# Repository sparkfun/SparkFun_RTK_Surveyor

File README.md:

SparkFun RTK Surveyor - Hardware
===========================================================

[*SparkFun RTK Surveyor (SPX-17369)*](https://www.sparkfun.com/products/17369)

The SparkFun RTK Surveyor is an easy to use GNSS receiver for centimeter-level positioning. Perfect for surveying, this preprogrammed device can also be used for autonomous driving, navigation, asset tracking and any other application where there is a clear view of the sky. The RTK Surveyor can also be used as a base station. With the flick of a switch, two RTK Surveyors can be used to create an RTK system capable of 14mm horizontal positional accuracy. The built-in Bluetooth connection via an ESP32 WROOM enables the user to use the RTK Surveyor with their choice of GIS application on a phone or tablet. The built in battery allows field use for up to four hours and is compatible with common USB battery banks.

This repo houses the hardware for the product including the PCB design, enclosure, and graphic overlay. The firmware for the RTK Surveyor (and other SparkFun RTK products) can be found [here](https://github.com/sparkfun/SparkFun_RTK_Firmware).

SparkFun labored with love to create this product. Feel like supporting open source hardware? 
[Buy a product](https://www.sparkfun.com/products/17369) from SparkFun!

Repository Contents
-------------------

* **/Documents** - Documentation on hardware and 3D files for the enclosure
* **/Enclosure** - gcode for enclosure milling
* **/Graphics** - Bitmaps for display (not currently implmented)
* **/Hardware** - Eagle files

Documentation
--------------

* **[Hookup Guide](https://learn.sparkfun.com/tutorials/sparkfun-rtk-surveyor-hookup-guide)** - Hookup guide for the SparkFun RTK Surveyor.

License Information
-------------------

This product is _**open source**_!

Various bits of the code have different licenses applied. Anything SparkFun wrote is beerware; if you see me (or any other SparkFun employee) at the local, and you've found our code helpful, please buy us a round!

Please use, reuse, and modify these files as you see fit. Please maintain attribution to SparkFun Electronics and release anything derivative under the same license.

Distributed as-is; no warranty is given.

- Your friends at SparkFun.

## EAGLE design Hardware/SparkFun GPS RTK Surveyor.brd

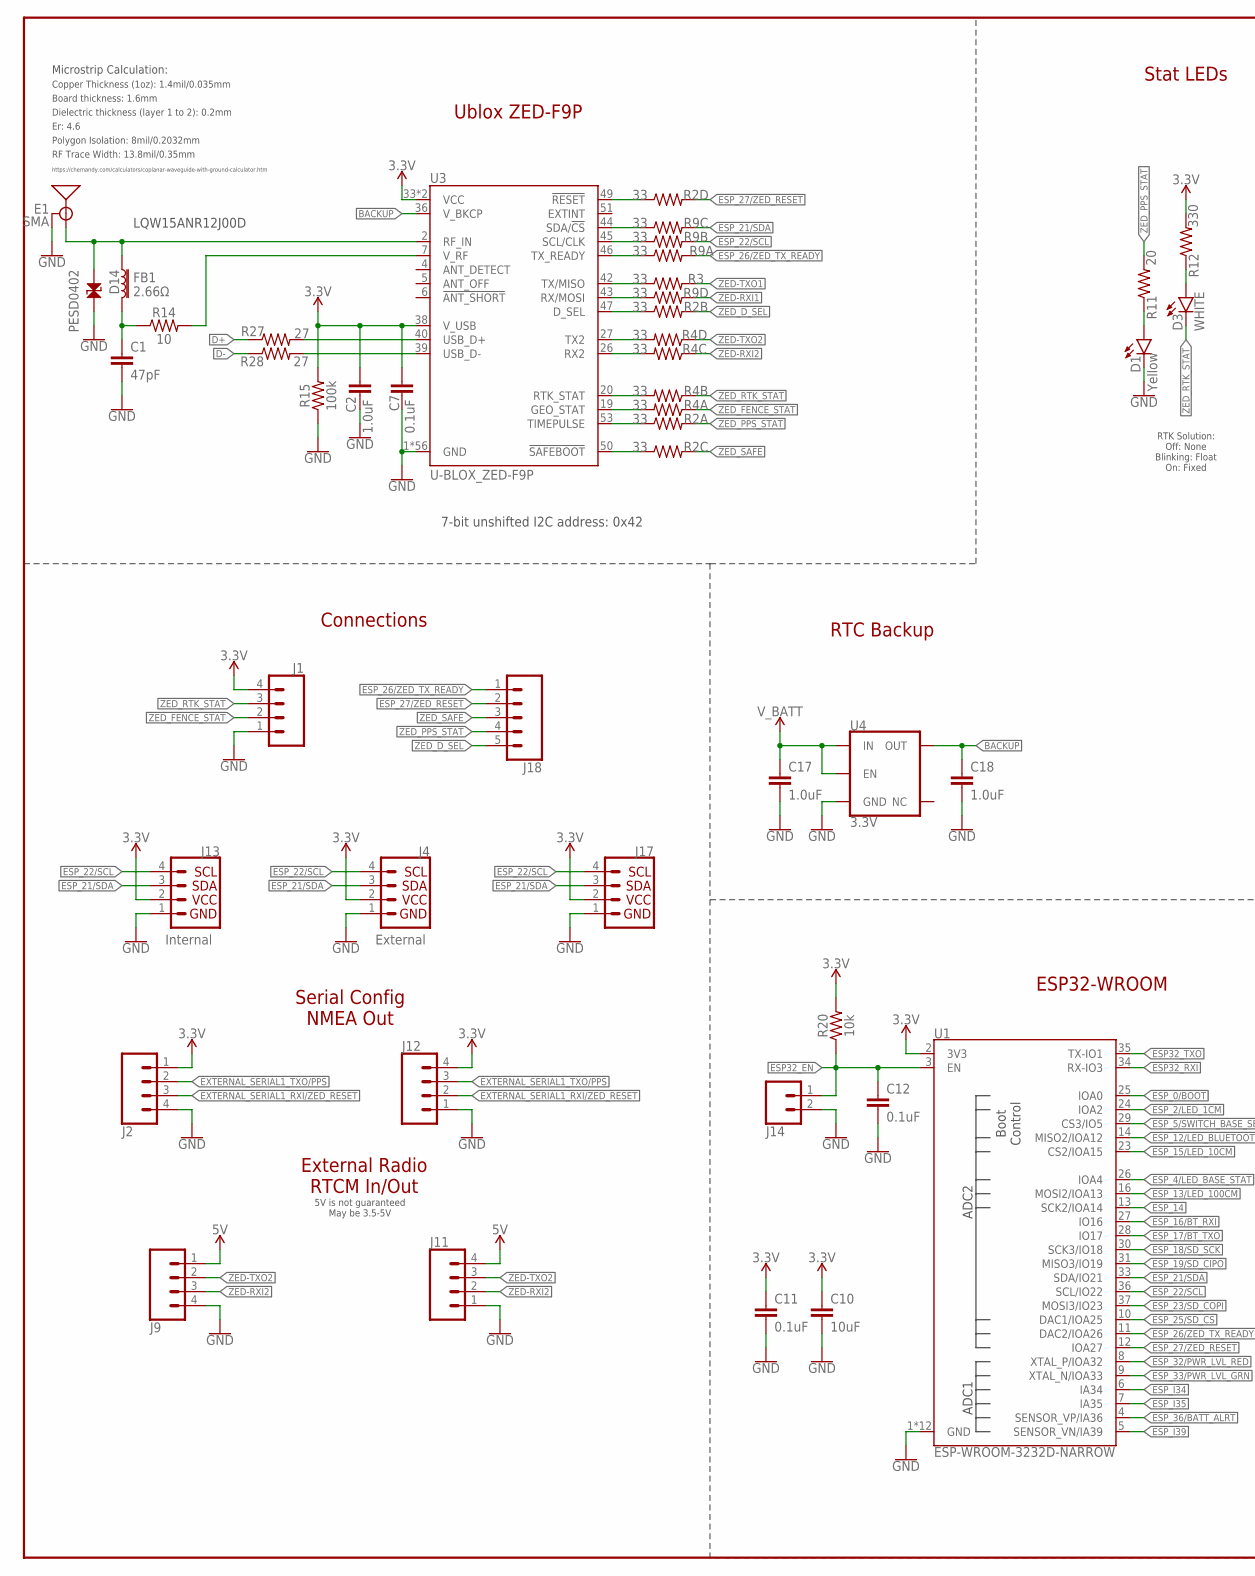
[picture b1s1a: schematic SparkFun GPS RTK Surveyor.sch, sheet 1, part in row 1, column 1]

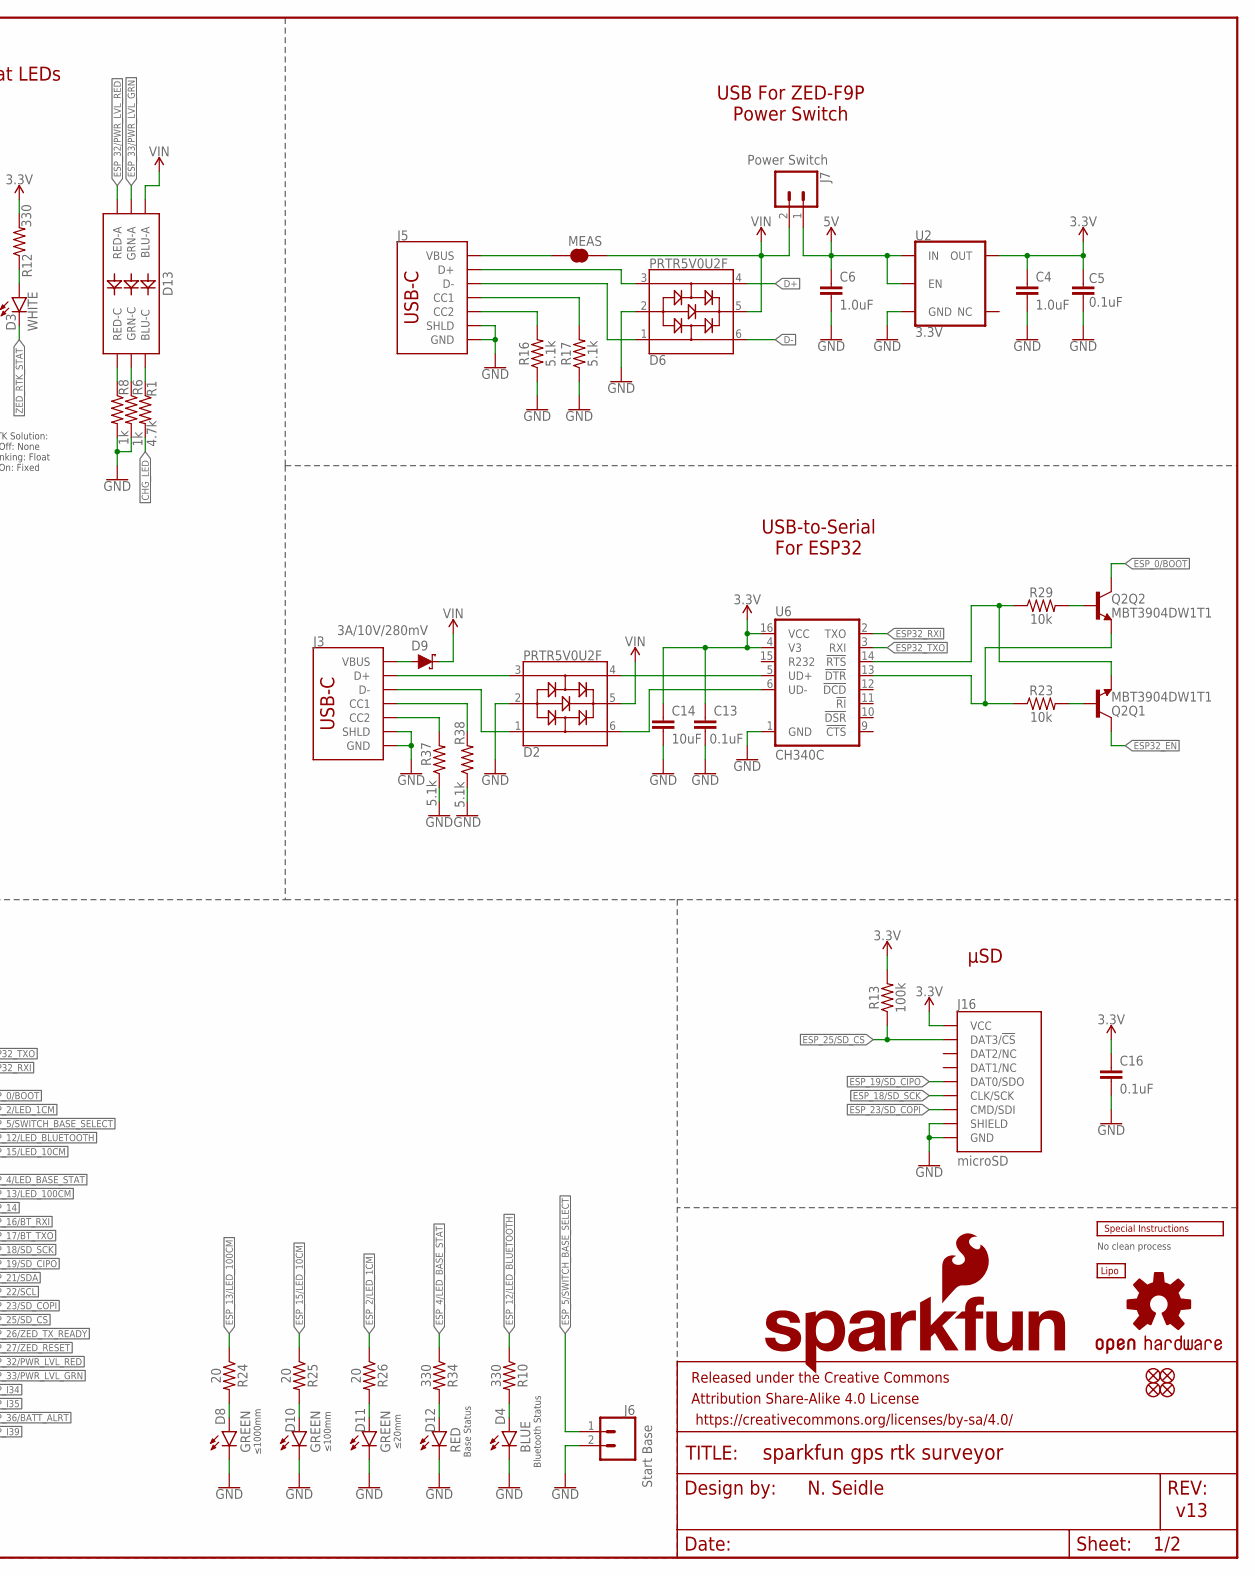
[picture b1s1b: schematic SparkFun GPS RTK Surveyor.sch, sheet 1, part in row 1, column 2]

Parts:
BT1: LIPO-OUTLINE1000; LIPO-1000
C1: 47pF; 0402
C2, C4, C6, C17, C18: 1.0uF; 0603
C5, C7, C11, C12, C13, C16: 0.1uF; 0603
C10, C14: 10uF; 0603
D1: Yellow; LED-0603
D2, D6: PRTR5V0U2F; SOT886
D3: WHITE; LED-0603
D4: BLUE; LED-0603
D8, D10, D11: GREEN; LED-0603
D9: 3A/10V/280mV; SOD-323
D12: RED; LED-0603
D13: LED-RGBBRG; LED-TRICOLOR-5050
D14: PESD0402; 0402
E1: SMA; SMA-EDGE
FB1: 2.66Ω; 0402-TIGHT
FRAME2: FRAME-LEDGER; CREATIVE_COMMONS
J1, J11, J12: CONN_041X04_NO_SILK_NO_POP; 1X04_NO_SILK
J2, J9: CONN_04JST-SMD-LOCKING; JST-4-SMD-1.25MM-LOCKING
J3, J5: USB Female Type C Connector; USB-C-16P_4LAYER-PADS
J4: External; JST04_1MM_RA
J6: Start Base; JST-2-SMD
J7: Power Switch; JST-2-SMD
J13: Internal; JST04_1MM_RA
J14: CONN_021X02_NO_SILK; 1X02_NO_SILK
J16: microSD; MICRO-SD-SOCKET
J17: Qwiic Right Angle; 1X04_NO_SILK
J18: CONN_05NO_SILK; 1X05_NO_SILK
JP21, JP61, JP71, JP81: FIDUCIALUFIDUCIAL; FIDUCIAL-MICRO
LOGO1: OSHW-LOGOMINI; OSHW-LOGO-MINI
LOGO2: SFE_LOGO_NAME_FLAME.1_INCH; SFE_LOGO_NAME_FLAME_.1
MEAS: JUMPER-COMBO_2_NC_TRACE; COMBO-JUMPER_2_NC_TRACE
Q2: MBT3904DW1T1; SC70-6
R1: 4.7k; 0603
R2, R4, R9: 33; 1206_RA
R3: 33; 0603
R6, R8: 1k; 0603
R10, R12, R34: 330; 0603
R11, R24, R25, R26: 20; 0603
R13, R15: 100k; 0603
R14: 10; 0603
R16, R17, R37, R38: 5.1k; 0603
R20, R23, R29: 10k; 0603
R27, R28: 27; 0603
U1: ESP-WROOM-3232D-NARROW; ESP-WROOM-32D-NARROW
U2, U4: 3.3V; SOT23-5
U3: U-BLOX_ZED-F9P; ZED-F9P
U6: CH340C; SO016
U$2: SPECIAL_INSTRUCTIONS-ORDERING; ORDERING_INSTRUCTIONS

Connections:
3.3V: C2.1, C4.1, C5.2, C7.2, C10.1, C11.1, C13.1, C14.1, C16.1, J1.4, J2.1, J4.2, J12.4, J13.2, J16.VCC, J17.2, R12.2, R13.2, R15.2, R20.2, U1.2 (3V3), U2.5 (OUT), U3.33 (VCC), U3.34 (VCC), U3.38 (V_USB), U6.4 (V3), U6.16 (VCC)
5V: C6.1, J7.1 (2), J9.1, J11.4, U2.1 (IN), U2.3 (EN)
ANT_VCC: C1.1, FB1.2, R14.1
BACKUP: C18.1, U3.36 (V_BKCP), U4.5 (OUT)
CC1: J5.A5 (CC1), R17.2
CC2: J5.B5 (CC2), R16.2
CC3: J3.B5 (CC2), R37.2
CC4: J3.A5 (CC1), R38.2
CHG_LED: R1.2; also elsewhere on the board
D+: D6.4, R27.1
D+1: D2.4, U6.5 (UD+)
D-: D6.6, R28.1
D-1: D2.6, U6.6 (UD-)
ESP32_!DTR: Q2.1 (E), R23.1, U6.13 (!DTR)
ESP32_!RTS: Q2.4 (E), R29.1, U6.14 (!RTS)
ESP32_EN: C12.1, J14.1, Q2.3 (C), R20.1, U1.3 (EN)
ESP32_RXI: U1.34 (RX-IO3), U6.2 (TXO)
ESP32_TXO: U1.35 (TX-IO1), U6.3 (RXI)
ESP_0/BOOT: Q2.6 (C), U1.25 (IOA0)
ESP_2/LED_1CM: R26.1, U1.24 (IOA2)
ESP_4/LED_BASE_STAT: R34.1, U1.26 (IOA4)
ESP_5/SWITCH_BASE_SELECT: J6.1 (2), U1.29 (CS3/IO5)
ESP_12/LED_BLUETOOTH: R10.1, U1.14 (MISO2/IOA12)
ESP_13/LED_100CM: R24.1, U1.16 (MOSI2/IOA13)
ESP_14: U1.13 (SCK2/IOA14)
ESP_15/LED_10CM: R25.1, U1.23 (CS2/IOA15)
ESP_16/BT_RXI: U1.27 (IO16); also elsewhere on the board
ESP_17/BT_TXO: U1.28 (IO17); also elsewhere on the board
ESP_18/SD_SCK: J16.SCLK (CLK/SCK), U1.30 (SCK3/IO18)
ESP_19/SD_CIPO: J16.DO/DAT0 (DAT0/SDO), U1.31 (MISO3/IO19)
ESP_21/SDA: J4.3, J13.3, J17.3, R9.P6 (2), U1.33 (SDA/IO21); also elsewhere on the board
ESP_22/SCL: J4.4, J13.4, J17.4, R9.P7 (2), U1.36 (SCL/IO22); also elsewhere on the board
ESP_23/SD_COPI: J16.DI/CMD (CMD/SDI), U1.37 (MOSI3/IO23)
ESP_25/SD_!CS!: J16.CS/DAT3 (DAT3/!CS!), R13.1, U1.10 (DAC1/IOA25)
ESP_26/ZED_TX_READY: J18.1, R9.P8 (2), U1.11 (DAC2/IOA26)
ESP_26/ZED_TX_READY_LV: R9.P1 (1), U3.46 (TX_READY)
ESP_27/ZED_!RESET!: J18.2, R2.P5 (2), U1.12 (IOA27); also elsewhere on the board
ESP_27/ZED_!RESET!_LV: R2.P4 (1), U3.49 (!RESET!)
ESP_32/PWR_LVL_RED: D13.5 (RED-A), U1.8 (XTAL_P/IOA32)
ESP_33/PWR_LVL_GRN: D13.4 (GRN-A), U1.9 (XTAL_N/IOA33)
ESP_36/BATT_ALRT: U1.4 (SENSOR_VP/IA36); also elsewhere on the board
ESP_D1+: D2.3, J3.A6 (D+), J3.B6 (D+)
ESP_D1-: D2.1, J3.A7 (D-), J3.B7 (D-)
ESP_I34: U1.6 (IA34)
ESP_I35: U1.7 (IA35)
ESP_I39: U1.5 (SENSOR_VN/IA39)
EXTERNAL_SERIAL1_RXI/ZED_!RESET!: J2.3, J12.2; also elsewhere on the board
EXTERNAL_SERIAL1_TXO/PPS: J2.2, J12.3; also elsewhere on the board
FENCE_LV: R4.P8 (2), U3.19 (GEO_STAT)
GND: C1.2, C2.2, C4.2, C5.1, C6.2, C7.1, C10.2, C11.2, C12.2, C13.2, C14.2, C16.2, C17.2, C18.2, D1.C, D2.2, D4.C, D6.2, D8.C, D10.C, D11.C, D12.C, D14.2, E1.GND@0 (GND), E1.GND@1 (GND), E1.GND@2 (GND), E1.GND@3 (GND), J1.1, J2.4, J3.GND, J3.GND2 (GND), J3.SHLD1 (SHLD), J3.SHLD2 (SHLD), J3.SHLD3 (SHLD), J3.SHLD4 (SHLD), J4.1, J5.GND, J5.GND2 (GND), J5.SHLD1 (SHLD), J5.SHLD2 (SHLD), J5.SHLD3 (SHLD), J5.SHLD4 (SHLD), J6.2 (1), J9.4, J11.1, J12.1, J13.1, J14.2, J16.CD1 (SHIELD), J16.GND, J16.GND1 (GND), J16.GND3 (GND), J17.1, R6.2, R8.2, R15.1, R16.1, R17.1, R37.1, R38.1, U1.1 (GND), U1.15 (GND), U1.38 (GND), U1.GND1 (GND), U1.GNDT1 (GND), U1.GNDT2 (GND), U1.GNDT3 (GND), U1.GNDT4 (GND), U1.GNDT5 (GND), U1.GNDT6 (GND), U1.GNDT7 (GND), U1.GNDT8 (GND), U2.2 (GND), U3.1 (GND), U3.3 (GND), U3.12 (GND), U3.14 (GND), U3.32 (GND), U3.37 (GND), U3.41 (GND), U3.48 (GND), U3.55 (GND), U3.56 (GND), U3.57 (GND), U3.58 (GND), U3.59 (GND), U3.60 (GND), U3.61 (GND), U3.62 (GND), U3.63 (GND), U3.64 (GND), U3.65 (GND), U3.66 (GND), U3.67 (GND), U3.68 (GND), U3.69 (GND), U3.70 (GND), U3.71 (GND), U3.72 (GND), U3.73 (GND), U3.74 (GND), U3.75 (GND), U3.76 (GND), U3.77 (GND), U3.78 (GND), U3.79 (GND), U3.80 (GND), U3.81 (GND), U3.82 (GND), U3.83 (GND), U3.84 (GND), U3.85 (GND), U3.86 (GND), U3.87 (GND), U3.88 (GND), U3.89 (GND), U3.90 (GND), U3.91 (GND), U3.92 (GND), U3.93 (GND), U3.94 (GND), U3.95 (GND), U3.96 (GND), U3.97 (GND), U3.98 (GND), U3.99 (GND), U3.100 (GND), U3.101 (GND), U3.102 (GND), U4.2 (GND), U6.1 (GND); also elsewhere on the board
GPS_ANT1: D14.1, E1.SIG (SIGNAL), FB1.1, U3.2 (RF_IN)
unnamed: D3.A, R12.1
unnamed: D1.A, R11.1
unnamed: D4.A, R10.2
unnamed: J5.VBUS1 (VBUS), J5.VBUS2 (VBUS), MEAS.1, MEAS.3 (1)
unnamed: D13.1 (BLU-C), R1.1
unnamed: D13.3 (GRN-C), R6.1
unnamed: D13.2 (RED-C), R8.1
unnamed: R27.2, U3.40 (USB_D+)
unnamed: R28.2, U3.39 (USB_D-)
unnamed: R14.2, U3.7 (V_RF)
unnamed: Q2.5 (B), R23.2
unnamed: Q2.2 (B), R29.2
unnamed: D8.A, R24.2
unnamed: D10.A, R25.2
unnamed: D11.A, R26.2
unnamed: D12.A, R34.2
unnamed: D9.A, J3.VBUS1 (VBUS), J3.VBUS2 (VBUS)
PPS: R2.P1 (1), U3.53 (TIMEPULSE)
RTK_LV: R4.P7 (2), U3.20 (RTK_STAT)
RX2_LV: R4.P6 (2), U3.26 (RX2)
RXLV: R9.P4 (1), U3.43 (RX/MOSI)
SCL_LV: R9.P2 (1), U3.45 (SCL/CLK)
SDA_LV: R9.P3 (1), U3.44 (SDA/!CS!)
TX2_LV: R4.P5 (2), U3.27 (TX2)
TXLV: R3.1, U3.42 (TX/MISO)
UNP_D+: D6.3, J5.A6 (D+), J5.B6 (D+)
UNP_D-: D6.1, J5.A7 (D-), J5.B7 (D-)
VIN: D2.5, D6.5, D9.C, D13.6 (BLU-A), J7.2 (1), MEAS.2, MEAS.4 (2); also elsewhere on the board
V_BATT: C17.1, U4.1 (IN), U4.3 (EN); also elsewhere on the board
ZED-RXI1: R9.P5 (2); also elsewhere on the board
ZED-RXI2: J9.3, J11.2, R4.P3 (1); also elsewhere on the board
ZED-TXO1: R3.2; also elsewhere on the board
ZED-TXO2: J9.2, J11.3, R4.P4 (1); also elsewhere on the board
ZED_!SAFE!: J18.3, R2.P6 (2)
ZED_!SAFE!_LV: R2.P3 (1), U3.50 (!SAFEBOOT!)
ZED_D_SEL: J18.5, R2.P7 (2)
ZED_D_SEL_LV: R2.P2 (1), U3.47 (D_SEL)
ZED_FENCE_STAT: J1.2, R4.P1 (1)
ZED_PPS_STAT: J18.4, R2.P8 (2), R11.2; also elsewhere on the board
ZED_RTK_STAT: D3.C, J1.3, R4.P2 (1)

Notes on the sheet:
v13
7-bit unshifted I2C address: 0x42
Ublox ZED-F9P
RTC Backup
Stat LEDs
LQW15ANR12J00D
Board thickness: 1.6mm
Er: 4.6
Copper Thickness (1oz): 1.4mil/0.035mm
RF Trace Width: 13.8mil/0.35mm
Polygon Isolation: 8mil/0.2032mm
No clean process
Dielectric thickness (layer 1 to 2): 0.2mm
https://chemandy.com/calculators/coplanar-waveguide-with-ground-calculator.htm
Microstrip Calculation:
Connections
External Radio RTCM In/Out
Serial Config NMEA Out
Base Status
≤1000mm
≤100mm
≤20mm
ESP32-WROOM
USB-to-Serial For ESP32
RTK Solution: Off: None Blinking: Float On: Fixed
Bluetooth Status
μSD
5V is not guaranteed May be 3.5-5V
USB For ZED-F9P Power Switch
N. Seidle

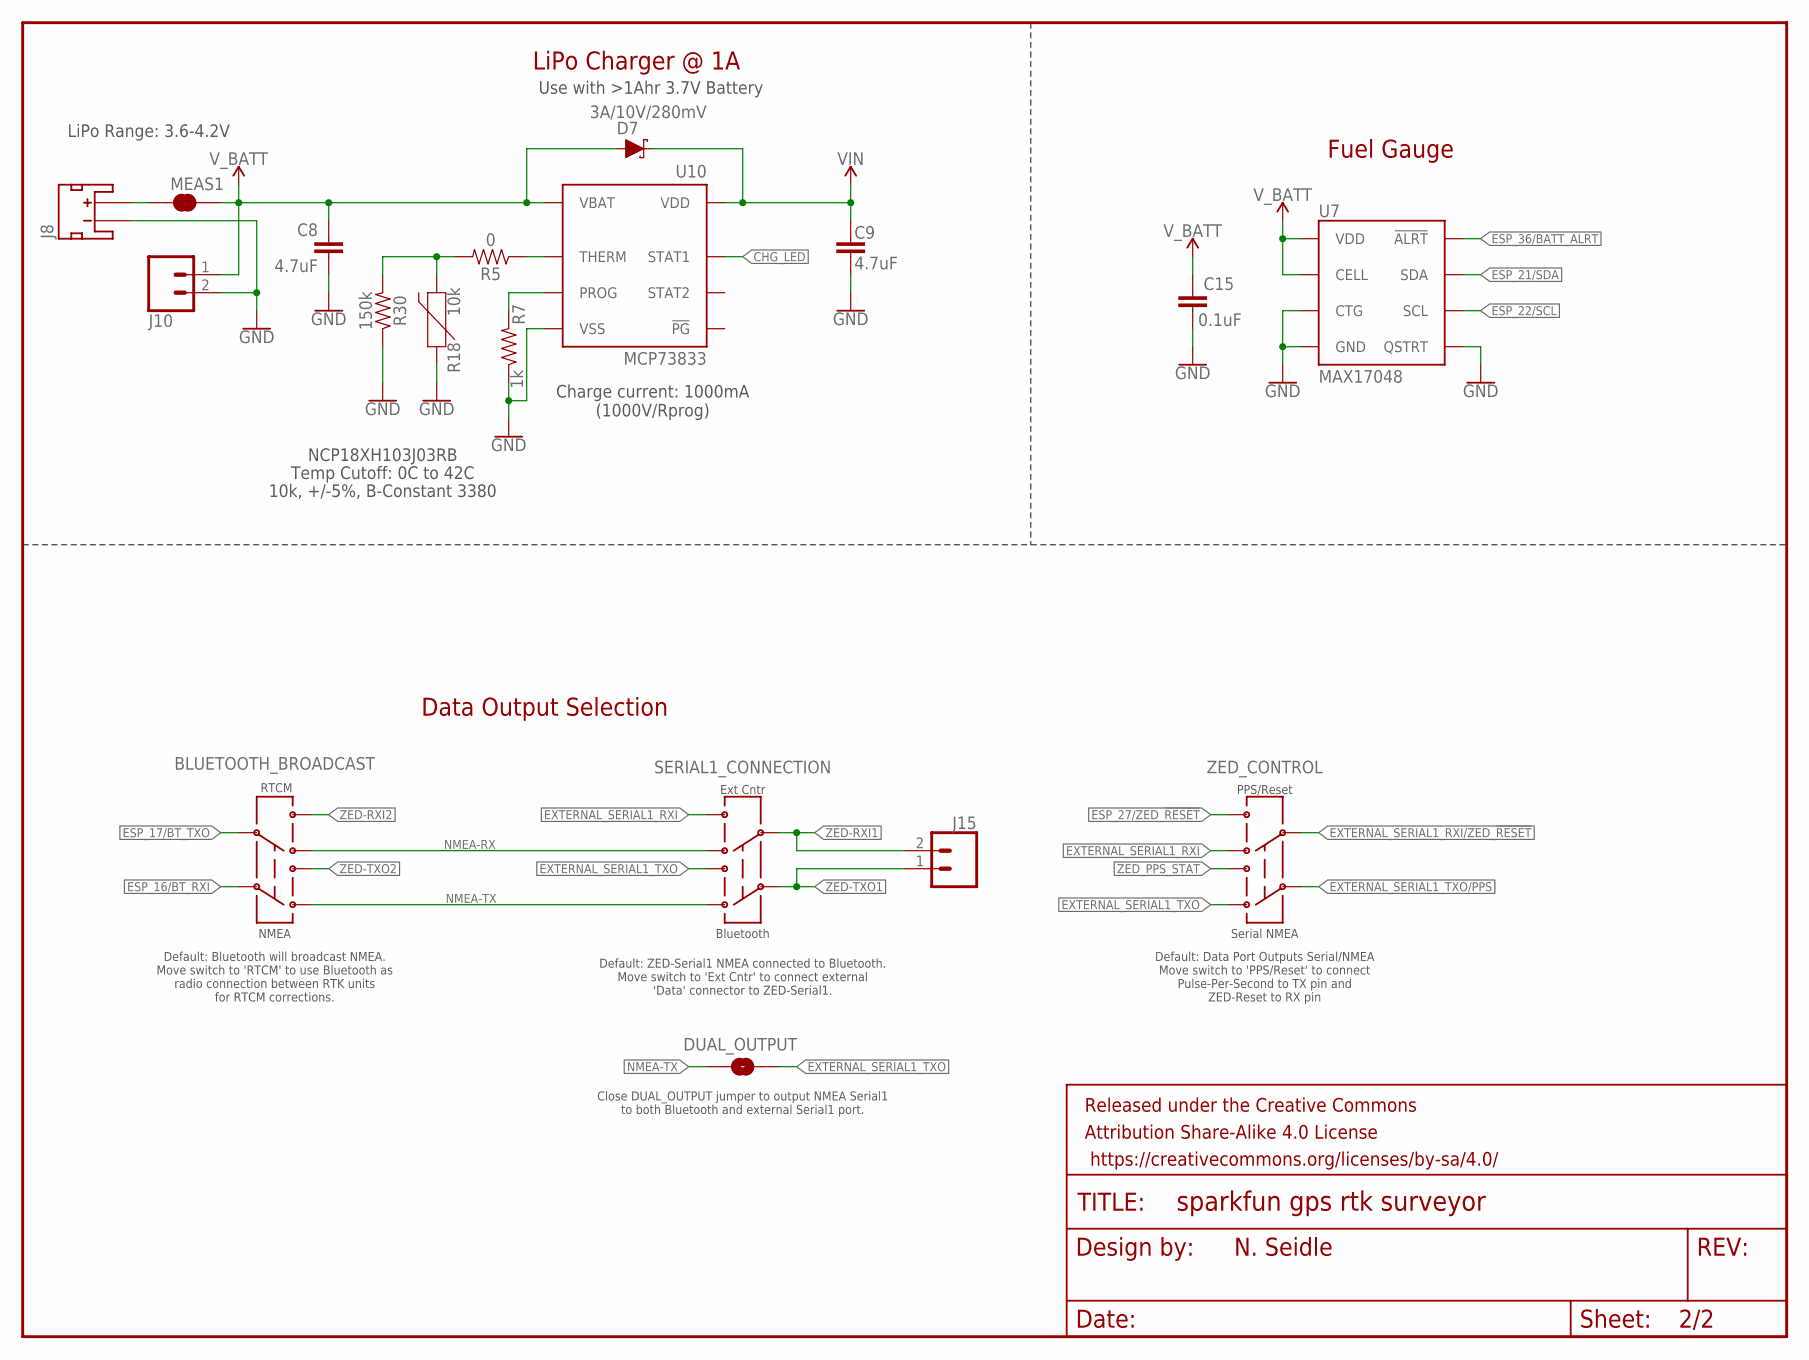
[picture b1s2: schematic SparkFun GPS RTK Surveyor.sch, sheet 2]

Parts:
BLUETOOTH_BROADCAST: SWITCH-DPDT-SMD-AYZ0202; SWITCH_DPDT_SMD_AYZ0202
C8, C9: 4.7uF; 0603
C15: 0.1uF; 0603
D7: 3A/10V/280mV; SOD-323
DUAL_OUTPUT: JUMPER-SMT_2_NO_SILK; SMT-JUMPER_2_NO_SILK
FRAME1: FRAME-LETTERNO_PACKAGE; DUMMY
J8: JST_2MM_MALE; JST-2-SMD
J10, J15: CONN_021X02_NO_SILK; 1X02_NO_SILK
MEAS1: JUMPER-COMBO_2_NC_TRACE; COMBO-JUMPER_2_NC_TRACE
R5: 0; 0603
R7: 1k; 0603
R18: 10k; 0603
R30: 150k; 0603
SERIAL1_CONNECTION: SWITCH-DPDT-SMD-AYZ0202; SWITCH_DPDT_SMD_AYZ0202
U7: MAX17048; DFN-8
U10: MCP73833; DFN-10
ZED_CONTROL: SWITCH-DPDT-SMD-AYZ0202; SWITCH_DPDT_SMD_AYZ0202

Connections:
CHG_LED: U10.3 (STAT1); also elsewhere on the board
CHG_THERM1: R5.2, R18.2, R30.2
ESP_16/BT_RXI: BLUETOOTH_BROADCAST.2; also elsewhere on the board
ESP_17/BT_TXO: BLUETOOTH_BROADCAST.5; also elsewhere on the board
ESP_21/SDA: U7.8 (SDA); also elsewhere on the board
ESP_22/SCL: U7.7 (SCL); also elsewhere on the board
ESP_27/ZED_!RESET!: ZED_CONTROL.4; also elsewhere on the board
ESP_36/BATT_ALRT: U7.5 (!ALRT); also elsewhere on the board
EXTERNAL_SERIAL1_RXI: SERIAL1_CONNECTION.4, ZED_CONTROL.6
EXTERNAL_SERIAL1_RXI/ZED_!RESET!: ZED_CONTROL.5; also elsewhere on the board
EXTERNAL_SERIAL1_TXO: DUAL_OUTPUT.2, SERIAL1_CONNECTION.1, ZED_CONTROL.3
EXTERNAL_SERIAL1_TXO/PPS: ZED_CONTROL.2; also elsewhere on the board
GND: C8.2, C9.2, C15.2, J8.1 (-), J10.2, R7.1, R18.1, R30.1, U7.1 (CTG), U7.4 (GND), U7.6 (QSTRT), U7.9 (GND), U10.5 (VSS), U10.11 (VSS); also elsewhere on the board
LIPO_RAW: J8.2 (+), MEAS1.1, MEAS1.3 (1)
unnamed: R5.1, U10.8 (THERM)
NMEA-RX: BLUETOOTH_BROADCAST.6, SERIAL1_CONNECTION.6
NMEA-TX: BLUETOOTH_BROADCAST.3, DUAL_OUTPUT.1, SERIAL1_CONNECTION.3
PROG1: R7.2, U10.6 (PROG)
VIN: C9.1, D7.C, U10.1 (VDD), U10.2 (VDD); also elsewhere on the board
V_BATT: C8.1, C15.1, D7.A, J10.1, MEAS1.2, MEAS1.4 (2), U7.2 (CELL), U7.3 (VDD), U10.9 (VBAT), U10.10 (VBAT); also elsewhere on the board
ZED-RXI1: J15.2, SERIAL1_CONNECTION.5; also elsewhere on the board
ZED-RXI2: BLUETOOTH_BROADCAST.4; also elsewhere on the board
ZED-TXO1: J15.1, SERIAL1_CONNECTION.2; also elsewhere on the board
ZED-TXO2: BLUETOOTH_BROADCAST.1; also elsewhere on the board
ZED_PPS_STAT: ZED_CONTROL.1; also elsewhere on the board

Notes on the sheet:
LiPo Range: 3.6-4.2V
Charge current: 1000mA (1000V/Rprog)
Use with >1Ahr 3.7V Battery
LiPo Charger @ 1A
NCP18XH103J03RB
10k, +/-5%, B-Constant 3380
Temp Cutoff: 0C to 42C
Fuel Gauge
Default: Bluetooth will broadcast NMEA. Move switch to 'RTCM' to use Bluetooth as radio connection between RTK units for RTCM corrections.
Default: ZED-Serial1 NMEA connected to Bluetooth. Move switch to 'Ext Cntr' to connect external 'Data' connector to ZED-Serial1.
Close DUAL_OUTPUT jumper to output NMEA Serial1 to both Bluetooth and external Serial1 port.
Data Output Selection
RTCM
NMEA
Ext Cntr
Bluetooth
N. Seidle
Default: Data Port Outputs Serial/NMEA Move switch to 'PPS/Reset' to connect Pulse-Per-Second to TX pin and ZED-Reset to RX pin
PPS/Reset
Serial NMEA

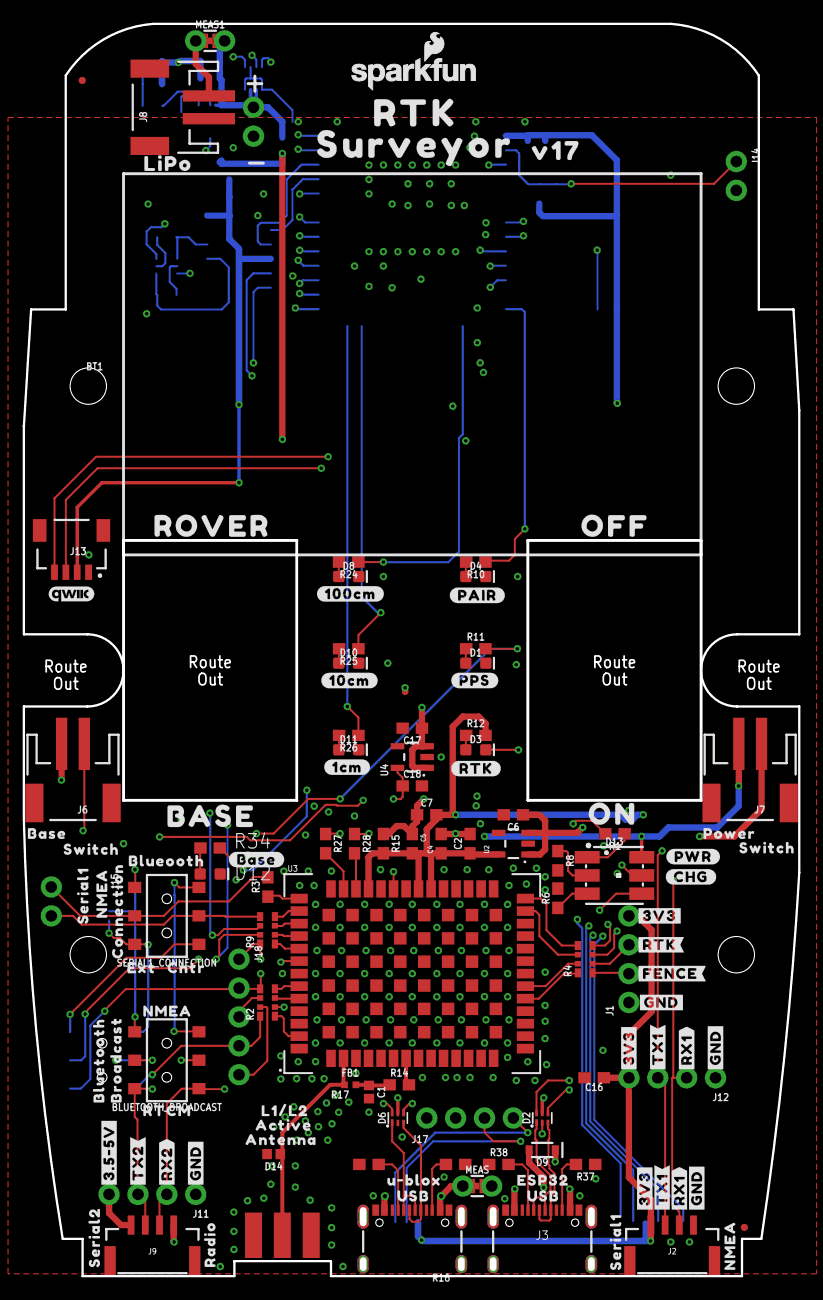
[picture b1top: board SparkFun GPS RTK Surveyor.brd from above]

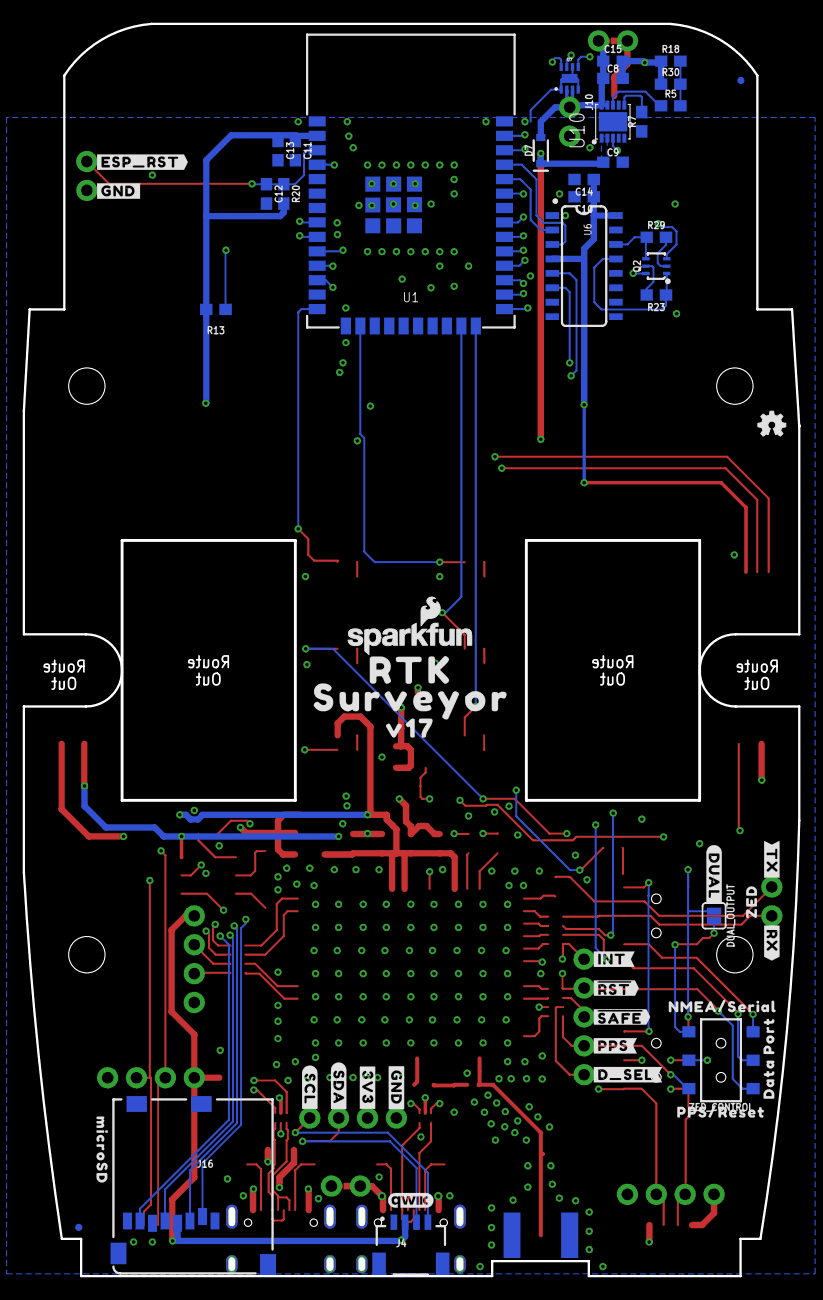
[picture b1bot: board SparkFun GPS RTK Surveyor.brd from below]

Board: 4 copper layers, 68.2 x 110.1 mm, 199 parts (55 on the bottom side), 95 nets.

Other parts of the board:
LOGO3: SFE_LOGO_NAME_FLAME.1_INCH; SFE_LOGO_NAME_FLAME_.1
U$1, U$38, U$48, U$82: #GND#0
U$3, U$34: ROCKER_SWITCH
U$4: #BASE#0
U$5, U$37, U$47: #3V3#0
U$6: ANTENNA0
U$7, U$74: RTK0
U$8: #CHG#0
U$9, U$71: _SURVEYOR3
U$10: #RTK#1
U$11: #PPS#0
U$12: #RTK#0
U$13, U$15, U$21, U$69, U$75, U$76, U$77, U$78: LIGHT_PIPE_3MM
U$14: #RX#2
U$16: ZED0
U$17: ##SAFE##5
U$18: ACTIVE0
U$19: L1#L21
U$20: #PAIR#0
U$22: BASE2
U$23: #3#5#5V#0
U$24: #PPS#1
U$25: #PWR#2
U$26: 1553DBK-ENCLOSURE
U$27: LIPO0
U$28: ##RST##4
U$29, U$63: SERIAL10
U$30, U$93: QWIIC_4MM
U$31: OFF1
U$32: #FENCE#3
U$33: #INT#0
U$35: U#BLOX0
U$36, U$66: USB1
U$39: #RX2#2
U$40: #TX2#1
U$41: BLUETOOTH2
U$42: ON0
U$43: SERIAL20
U$44: ROVER3
U$45, U$68: #RX1#2
U$46, U$65: #TX1#1
U$49, U$52: NMEA1
U$50: RADIO0
U$51: BROADCAST3
U$53: RTCM0
U$54: BASE0
U$55, U$57: SWITCH1
U$56: POWER0
U$58: BLUEOOTH3
U$59: CNTR1
U$60: #ESP_RST#0
U$61: EXT0
U$62: NMEA2
U$64: CONNECTION1
U$67: ESP320
U$70: #GND#2
U$72: #TX#1
U$73: #DUAL#0
U$79: #1CM#0
U$80: #10CM#1
U$81: #100CM#2
U$83: MICROSD0
U$84: #GND#1
U$85: #3V3#2
U$86: #SCL#1
U$87: #SDA#0
U$88: #D_SEL#0
U$89: DATA2
U$90: PORT3
U$91: PPS#RESET0
U$92: NMEA#SERIAL1
U$94, U$95: V170

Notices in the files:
parts and their libraries:
SparkFun-Resistors: Licensing: Creative Commons ShareAlike 4.0 International - https://creativecommons.org/licenses/by-sa/4.0
SparkFun-Aesthetics: Released under the Creative Commons Attribution Share-Alike 4.0 License
SparkFun-Aesthetics: https://creativecommons.org/licenses/by-sa/4.0
